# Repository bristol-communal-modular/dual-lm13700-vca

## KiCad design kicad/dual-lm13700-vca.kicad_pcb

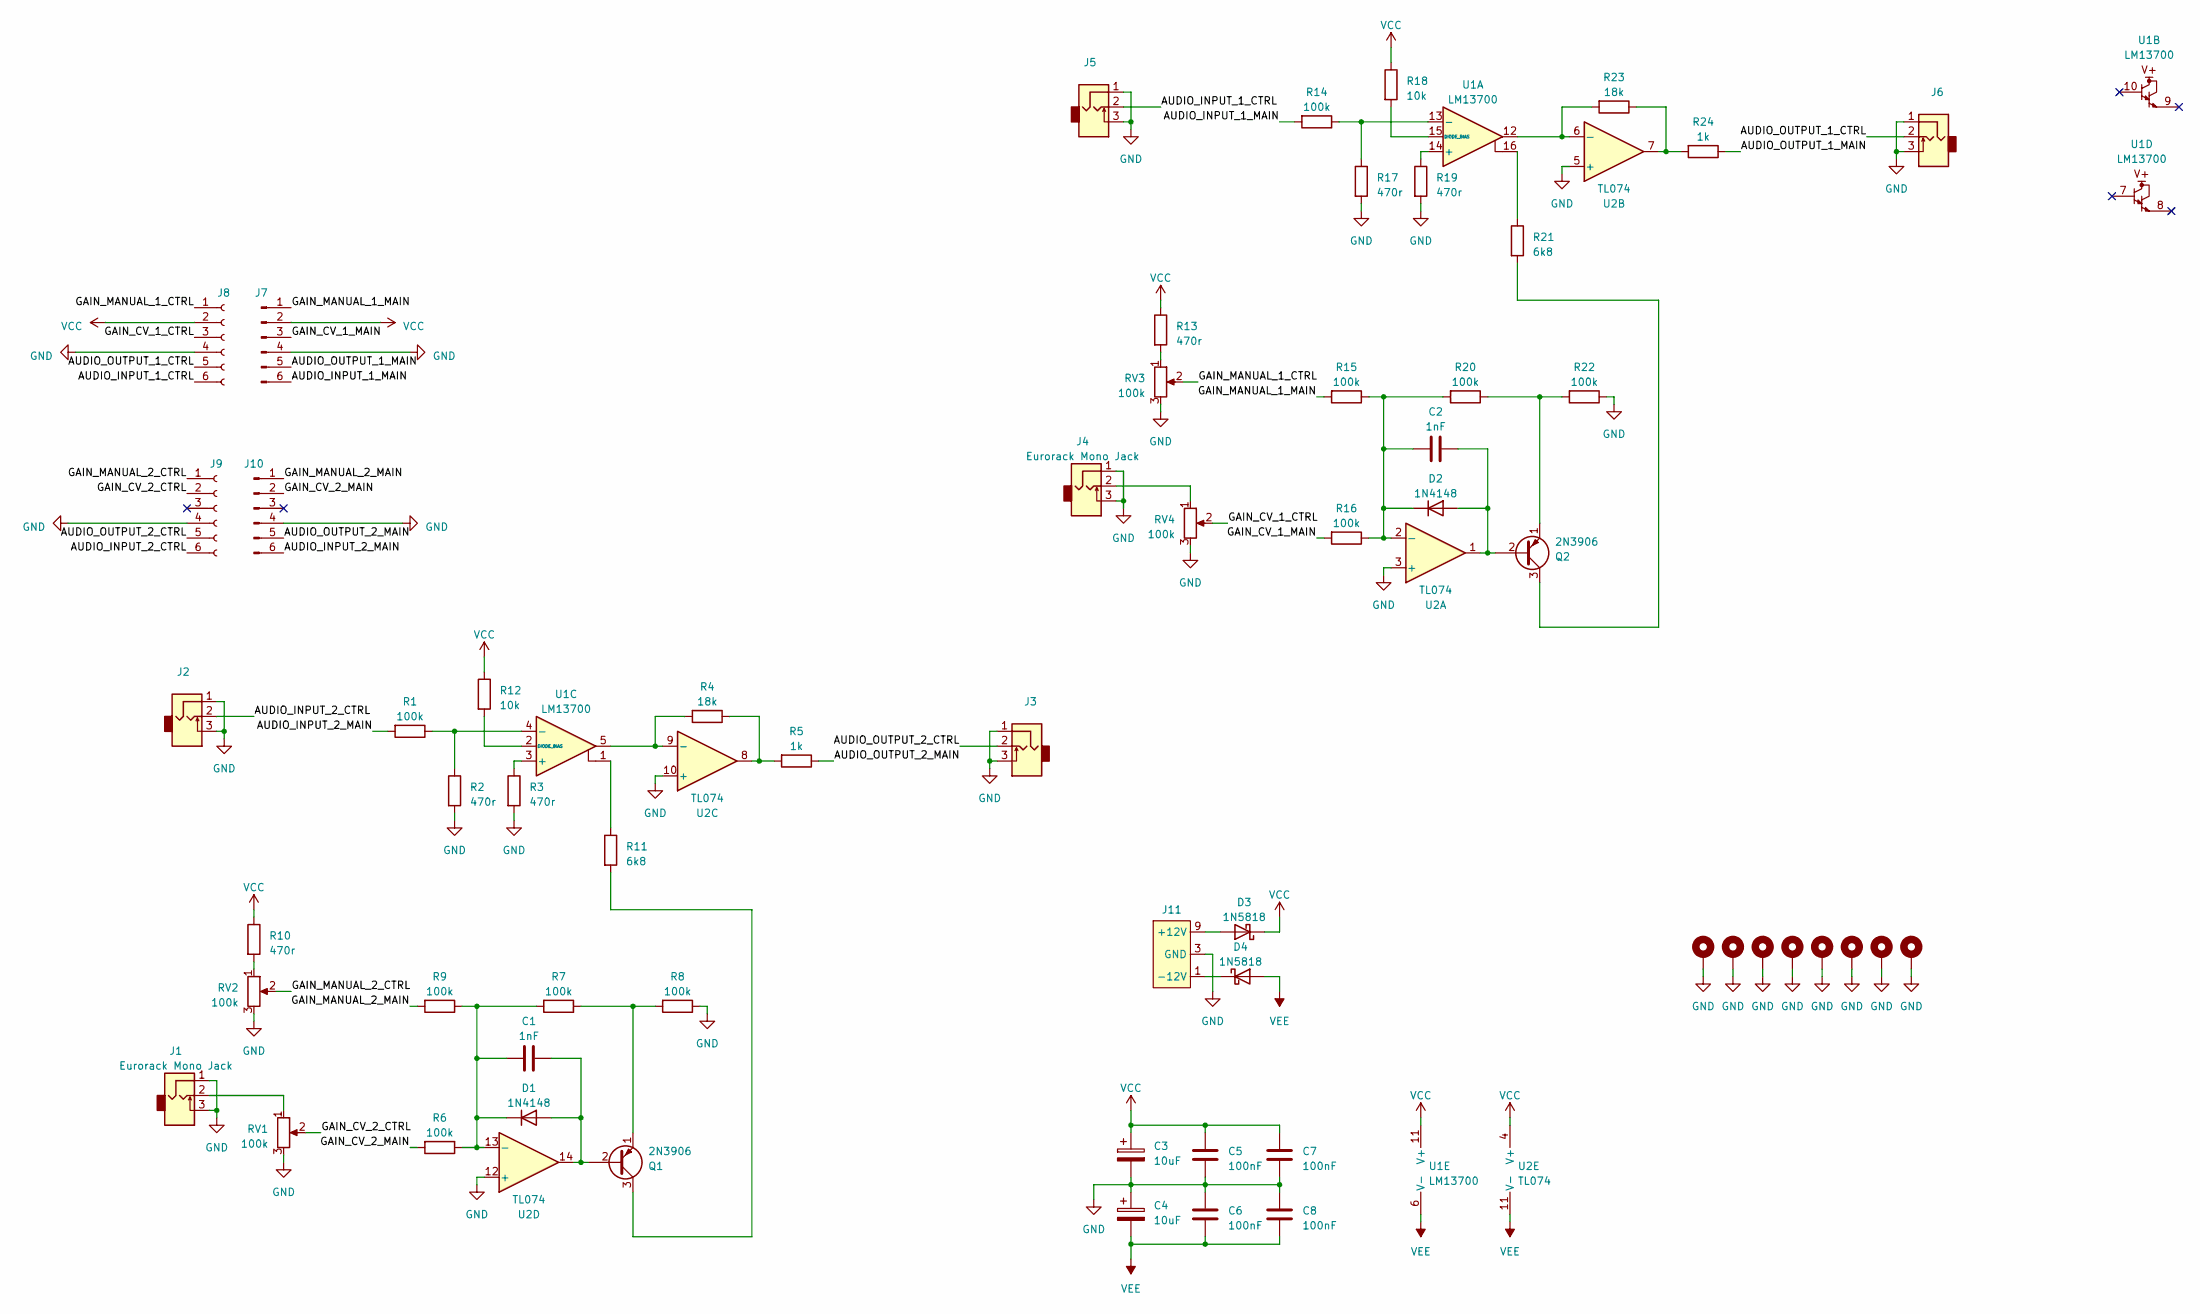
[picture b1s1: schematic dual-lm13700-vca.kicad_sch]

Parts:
C1, C2: 1nF; C_Rect_L7.0mm_W2.5mm_P5.00mm; Tolerance 5%
C3, C4: 10uF; CP_Radial_D5.0mm_P2.00mm; Tolerance 20%; Voltage 50v
C5, C6, C7, C8: 100nF; C_Rect_L7.0mm_W2.5mm_P5.00mm; Tolerance 5%
D1, D2: 1N4148; D_DO-35_SOD27_P7.62mm_Horizontal
D3, D4: 1N5818; D_DO-41_SOD81_P10.16mm_Horizontal
H1, H2, H3, H4, H5, H6, H7, H8: MountingHole_Pad; MountingHole_3.2mm_M3_DIN965_Pad
J1, J2, J3, J4, J5, J6: Eurorack Mono Jack; Jack_3.5mm_QingPu_WQP-PJ398SM_Vertical; mpn WQP-WQP518MA
J7, J10: Conn_01x06_Pin; PinHeader_1x06_P2.54mm_Vertical
J8, J9: Conn_01x06_Socket; PinSocket_1x06_P2.54mm_Vertical
J11: Eurorack Power Small; Eurorack_PowerHeader_2x05_P2.54mm_Shrouded
Q1, Q2: 2N3906; TO-92_Inline_Wide
R1, R6, R7, R8, R9, R14, R15, R16, R20, R22: 100k; R_Axial_DIN0207_L6.3mm_D2.5mm_P10.16mm_Horizontal; Tolerance 1%
R2, R3, R10, R13, R17, R19: 470r; R_Axial_DIN0207_L6.3mm_D2.5mm_P10.16mm_Horizontal; Tolerance 1%
R4, R23: 18k; R_Axial_DIN0207_L6.3mm_D2.5mm_P10.16mm_Horizontal; Tolerance 1%
R5, R24: 1k; R_Axial_DIN0207_L6.3mm_D2.5mm_P10.16mm_Horizontal; Tolerance 1%
R11, R21: 6k8; R_Axial_DIN0207_L6.3mm_D2.5mm_P10.16mm_Horizontal; Tolerance 1%
R12, R18: 10k; R_Axial_DIN0207_L6.3mm_D2.5mm_P10.16mm_Horizontal; Tolerance 1%
RV1, RV2, RV3, RV4: 100k; Potentiometer_Alpha_RD901F-40-00D_Single_Vertical
U1: LM13700; DIP-16_W7.62mm_Socket
U2: TL074; DIP-14_W7.62mm_Socket

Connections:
/AUDIO_INPUT_1_CTRL: J5.2 (Tip), J8.6
/AUDIO_INPUT_1_MAIN: J7.6, R14.2
/AUDIO_INPUT_2_CTRL: J2.2 (Tip), J9.6
/AUDIO_INPUT_2_MAIN: J10.6, R1.2
/AUDIO_OUTPUT_1_CTRL: J6.2 (Tip), J8.5
/AUDIO_OUTPUT_1_MAIN: J7.5, R24.1
/AUDIO_OUTPUT_2_CTRL: J3.2 (Tip), J9.5
/AUDIO_OUTPUT_2_MAIN: J10.5, R5.1
/GAIN_CV_1_CTRL: J8.3, RV4.2
/GAIN_CV_1_MAIN: J7.3, R16.2
/GAIN_CV_2_CTRL: J9.2, RV1.2
/GAIN_CV_2_MAIN: J10.2, R6.2
/GAIN_MANUAL_1_CTRL: J8.1, RV3.2
/GAIN_MANUAL_1_MAIN: J7.1, R15.2
/GAIN_MANUAL_2_CTRL: J9.1, RV2.2
/GAIN_MANUAL_2_MAIN: J10.1, R9.2
GND: C3.2, C4.1, C5.2, C6.1, C7.2, C8.1, H1.1, H2.1, H3.1, H4.1, H5.1, H6.1, H7.1, H8.1, J1.1 (Sleeve), J1.3 (Tip_normalize), J2.1 (Sleeve), J2.3 (Tip_normalize), J3.1 (Sleeve), J3.3 (Tip_normalize), J4.1 (Sleeve), J4.3 (Tip_normalize), J5.1 (Sleeve), J5.3 (Tip_normalize), J6.1 (Sleeve), J6.3 (Tip_normalize), J7.4, J8.4, J9.4, J10.4, J11.3 (GND), J11.4 (GND), J11.5 (GND), J11.6 (GND), J11.7 (GND), J11.8 (GND), R2.2, R3.2, R8.1, R17.2, R19.2, R22.1, RV1.3, RV2.3, RV3.3, RV4.3, U2.3 (+), U2.5 (+), U2.10 (+), U2.12 (+)
unnamed: C1.2, D1.2 (A), Q1.2 (B), U2.14
unnamed: C1.1, D1.1 (K), R6.1, R7.2, R9.1, U2.13 (-)
unnamed: C2.2, D2.2 (A), Q2.2 (B), U2.1
unnamed: C2.1, D2.1 (K), R15.1, R16.1, R20.2, U2.2 (-)
unnamed: D3.2 (A), J11.9 (+12V), J11.10 (+12V)
unnamed: D4.1 (K), J11.1 (-12V), J11.2 (-12V)
unnamed: J1.2 (Tip), RV1.1
unnamed: J4.2 (Tip), RV4.1
unnamed: Q1.3 (C), R11.2
unnamed: Q1.1 (E), R7.1, R8.2
unnamed: Q2.3 (C), R21.2
unnamed: Q2.1 (E), R20.1, R22.2
unnamed: R4.1, R5.2, U2.8
unnamed: R10.2, RV2.1
unnamed: R11.1, U1.1
unnamed: R13.2, RV3.1
unnamed: R21.1, U1.16
unnamed: R23.1, R24.2, U2.7
unnamed: R19.1, U1.14 (+)
unnamed: R14.1, R17.1, U1.13 (-)
unnamed: R18.2, U1.15 (DIODE_BIAS)
unnamed: R3.1, U1.3 (+)
unnamed: R1.1, R2.1, U1.4 (-)
unnamed: R12.2, U1.2 (DIODE_BIAS)
unnamed: R23.2, U1.12, U2.6 (-)
unnamed: R4.2, U1.5, U2.9 (-)
VCC: C3.1, C5.1, C7.1, D3.1 (K), J7.2, J8.2, R10.1, R12.1, R13.1, R18.1, U1.11 (V+), U2.4 (V+)
VEE: C4.2, C6.2, C8.2, D4.2 (A), U1.6 (V-), U2.11 (V-)

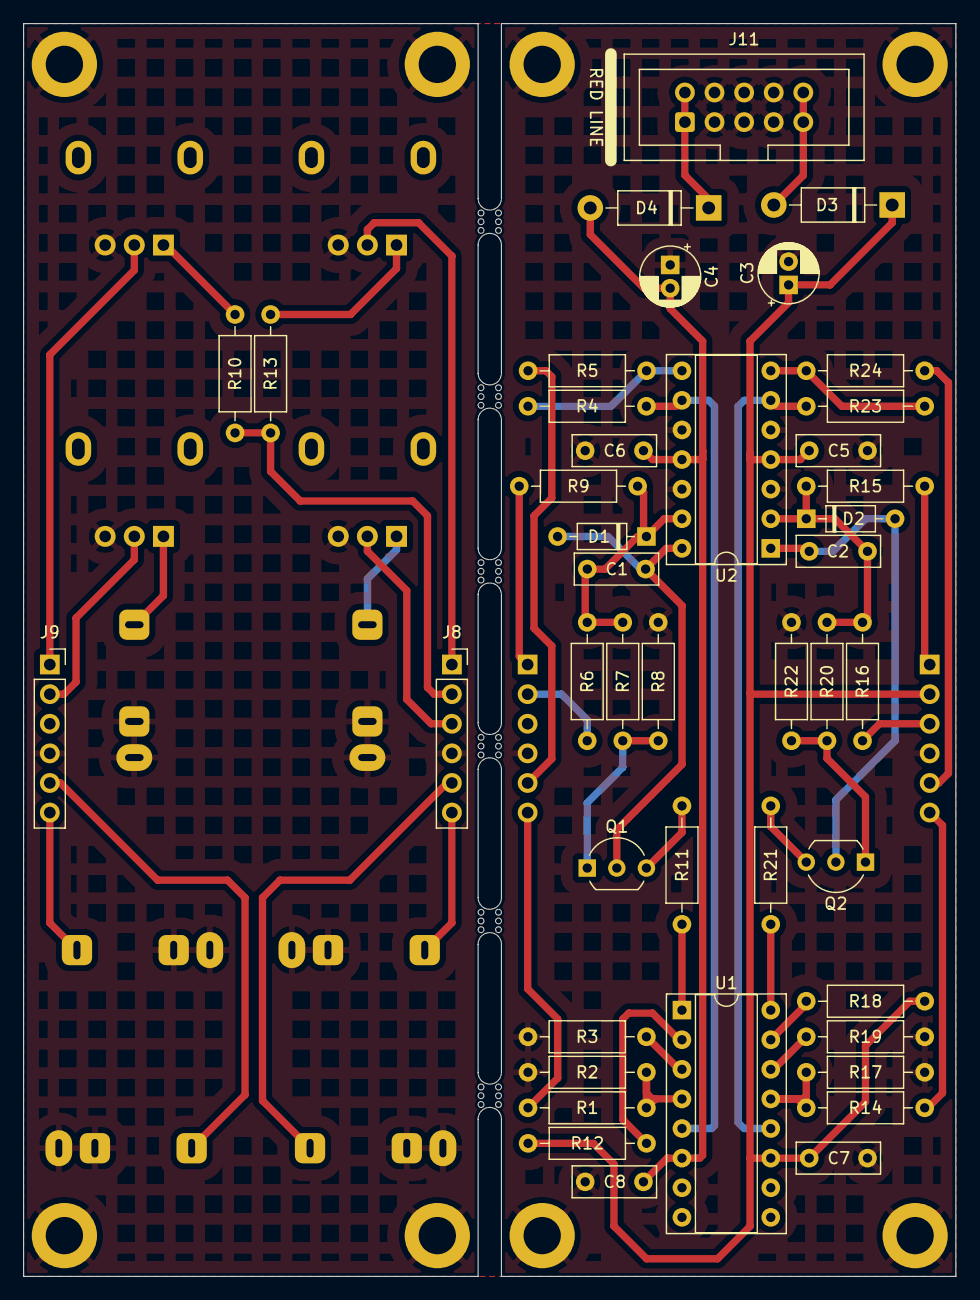
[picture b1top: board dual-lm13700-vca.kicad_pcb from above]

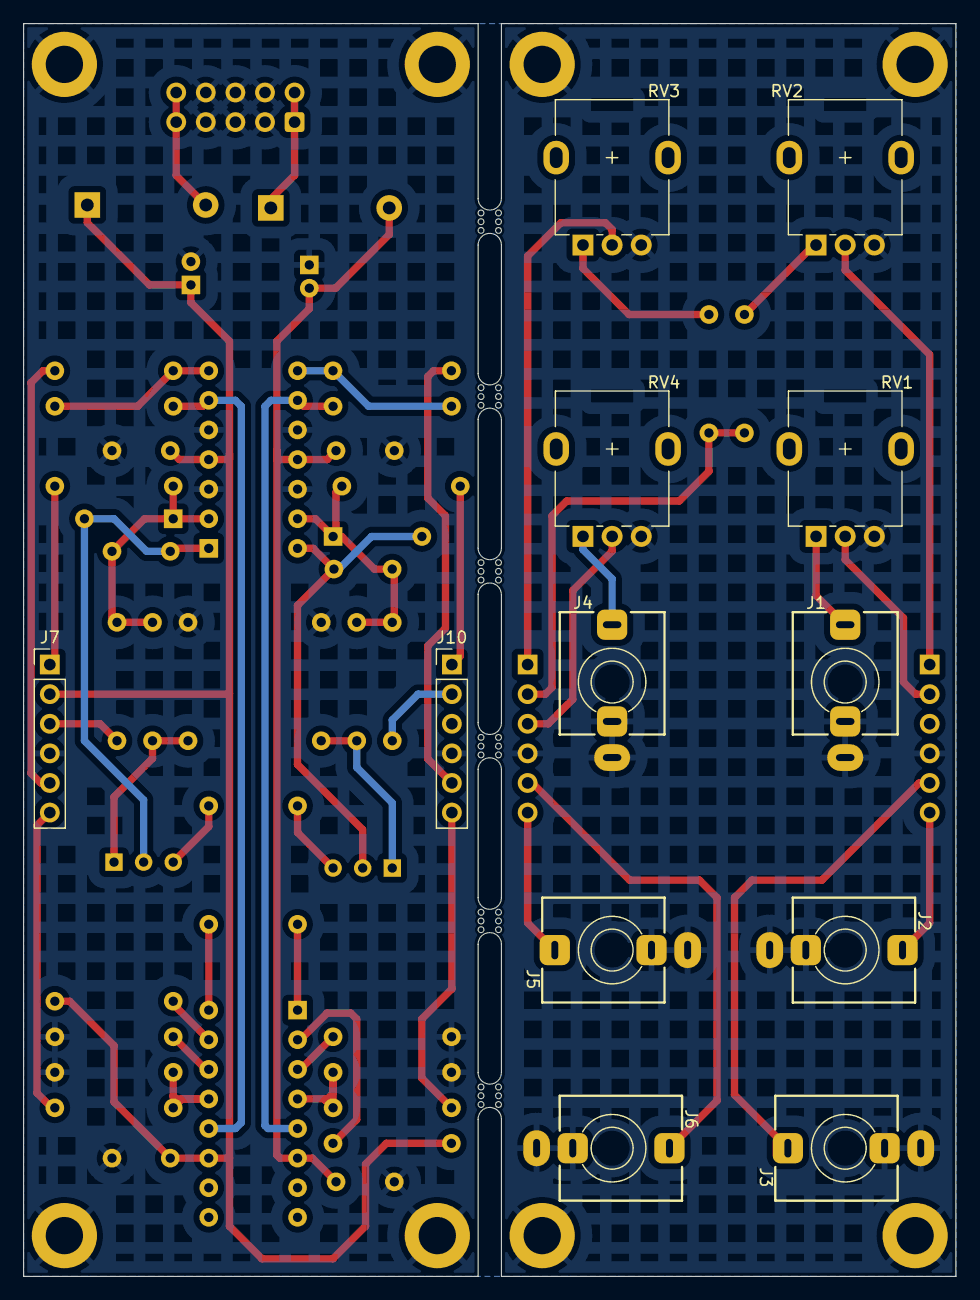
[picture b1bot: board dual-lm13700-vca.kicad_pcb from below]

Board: 2 copper layers, 80.0 x 107.5 mm, 69 parts (12 on the bottom side), 45 nets.

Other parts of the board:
mouse-bite-2mm-slot, mouse-bite-2mm-slot#2, mouse-bite-2mm-slot#3, mouse-bite-2mm-slot#4, mouse-bite-2mm-slot#5, mouse-bite-2mm-slot#6: VAL**; mouse-bite-2mm-slot

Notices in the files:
kicad/dual-lm13700-vca.kicad_pcb:
creativecommons.org/licenses/by/4.0
License: CC BY 4.0
